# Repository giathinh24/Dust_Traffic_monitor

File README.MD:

# Development manual

## Arduino_code directory
The file in this directory is coded in Arduino programming language, but is compiled and loaded to an ARM-based STM32 BluePill development board.
Product link: *https://hshop.vn/products/kit-ra-chon-stm32f103c8t6*

In order to achive this, the developer must first install the **STM32F1 boards (Arduino-STM32)** board manager. Then, inside Arduino IDE, the developer must change the board from **Arduino** to the correct STM32 board (For Blue Pill development board, its STM32F103C8T6). This will allow the user to program the STM32 board with ease by utilizing Arduino high-level features, instead of having to code in bare C.

To add STM32F1 board manager:
-Open File > Preference
-Paste this link into your *Additional Boards Manager URLs*: http://dan.drown.org/stm32duino/package_STM32duino_index.json
-Click OK
-Go to Tools > Board > Board manager
-Install *STM32F1xx/GD32F1xx board* package

Now you have STM32F1xx boards manager. To use, go to Tools > Board > STM32F1 boards > Select the right model (Likely the *Fake STM32F103C8* one)

Now you can compile Arduino code into STM32 bytecode. But to upload, you cannot use USB cable like an Arduino, but you have to buy an ST-Link device. Product link: https://hshop.vn/products/mach-nap-st-link-v2

Now you can code, compile, and upload to an STM32 board, congrats.

## RaspberryPi_code directory
This directory hold the Python code to run on Raspbery Pi device.

The main file is **Run.py** where all the code are.
**Set_wifi.py** automatically write a .conf file that can connect the device to a new Wifi network. The user will be prompted with the SSID and password. Once completed, restart the device, the new Wifi connection will take effect. Be careful that this will log the device out of the old network, so if you rely on SSH to connect to the Raspberry Pi device, this operation will log you out.
**Set_parameters.py** is used to set 5 parameters that are used by the Run.py script. These are:
-video_cut_interval: How long should each video be cut before sending to the cloud (unit in seconds)
-frame_rate: Frame rate of the video. Maximum 30. Recommended 10. Higher FPS means larger files (unit in FPS)
-node_name: Name of the current device. Used to reference the device on cloud data base.
-data_buffer_time: How long should the dust data (csv files) be kept on the internal storage before clean up (unit in days)
-video_buffer_time: How many videos can buffer before clean up. The Run script will take time to upload a video to the cloud, so a video has to be buffered until the upload operation is done, before we can delete it. But the internal device storage is limited, so we cannot buffer too much. This param set how many files can exist in the buffer storage. Chosing 5 will means the device will only buffer the most recent 5 videos, once a new video is added, the oldest one will be deleted to make room. Please make this choice base on how big is the device's internal storage.

## PCB directory
**DustSensorMk1.sch** is the schematic file describe the logical connection between components
**DustSensorMk1.brd** is the board file describe the physical layout of the PCB

**CAMOutputs** directory store the CAM files that are used for PCB miling machines.
For machines used at VGU, use files in the GerberFiles directory.

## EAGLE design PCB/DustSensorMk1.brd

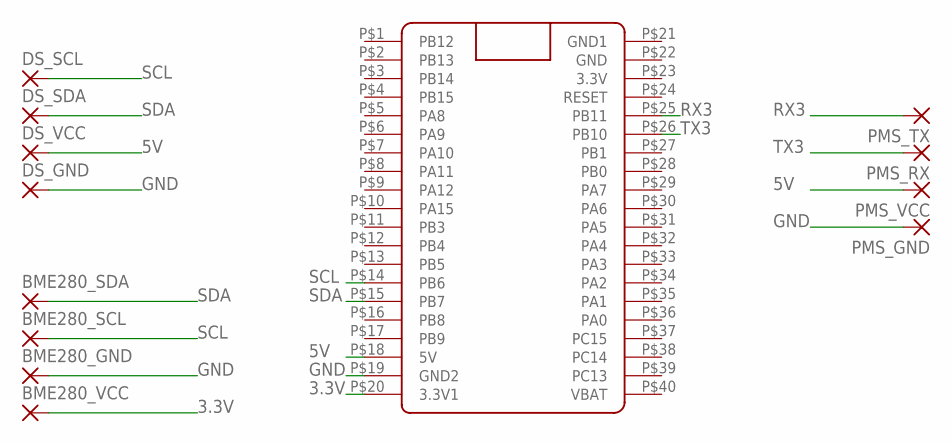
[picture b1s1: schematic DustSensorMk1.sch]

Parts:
BME280_GND, BME280_SCL, BME280_SDA, BME280_VCC: 2,15/1,0
DS_GND: 2,15/1,0
DS_SCL: 2,15/1,0
DS_SDA: 2,15/1,0
DS_VCC: 2,15/1,0
PMS_GND: 2,15/1,0
PMS_RX: 2,15/1,0
PMS_TX: 2,15/1,0
PMS_VCC: 2,15/1,0
U$1: BLUE_PILL

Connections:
3.3V: BME280_VCC.1, U$1.P$20 (3.3V1)
5V: DS_VCC.1, PMS_VCC.1, U$1.P$18 (5V)
GND: BME280_GND.1, DS_GND.1, PMS_GND.1, U$1.P$19 (GND2)
GND1: U$1.P$21 (GND1)
RX3: PMS_TX.1, U$1.P$25 (PB11)
SCL: BME280_SCL.1, DS_SCL.1, U$1.P$14 (PB6)
SDA: BME280_SDA.1, DS_SDA.1, U$1.P$15 (PB7)
TX3: PMS_RX.1, U$1.P$26 (PB10)

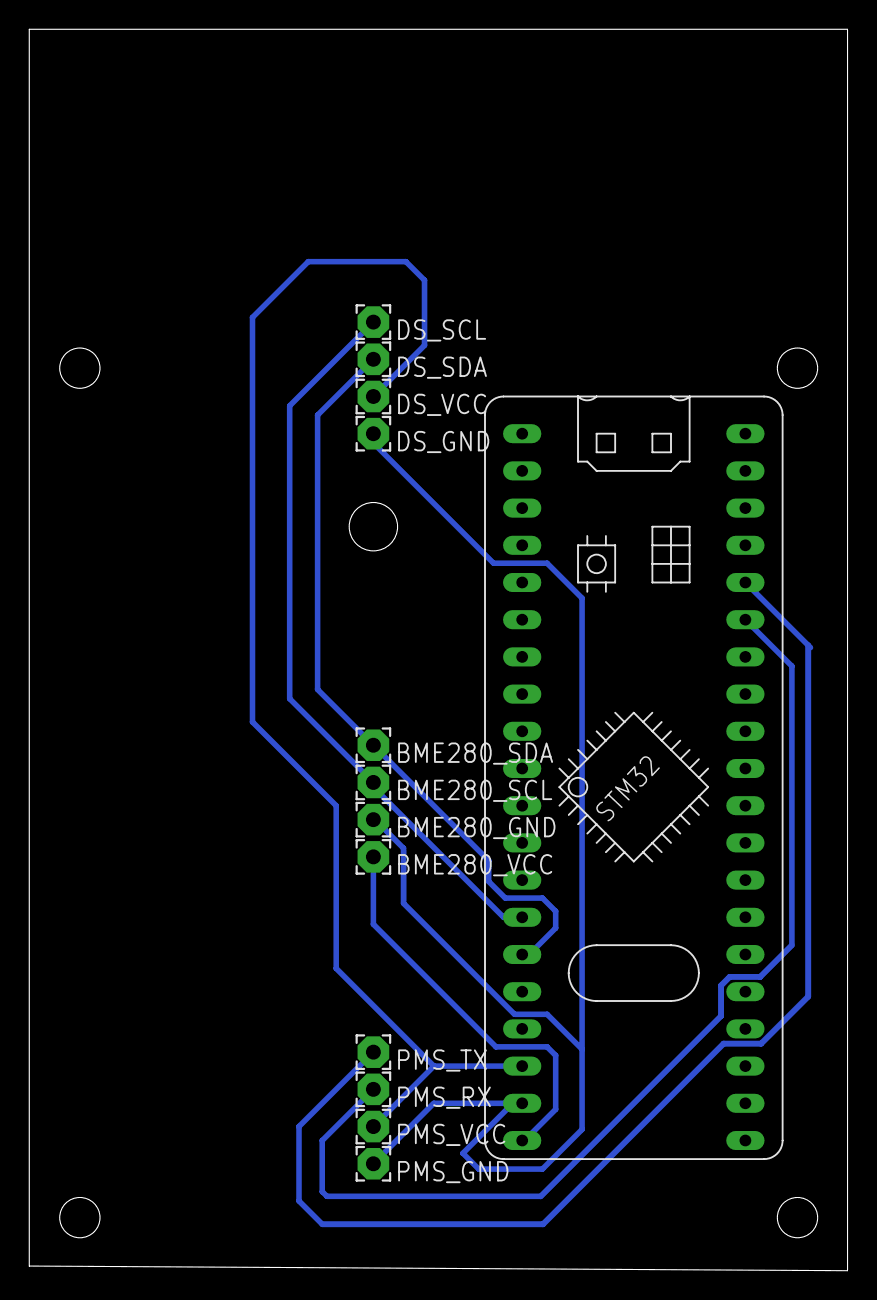
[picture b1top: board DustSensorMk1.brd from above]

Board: 2 copper layers, 55.9 x 84.8 mm, 13 parts (0 on the bottom side), 7 nets.

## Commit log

2024-03-13 Init repo
2024-03-13 Add images
2024-03-13 Fix images link
